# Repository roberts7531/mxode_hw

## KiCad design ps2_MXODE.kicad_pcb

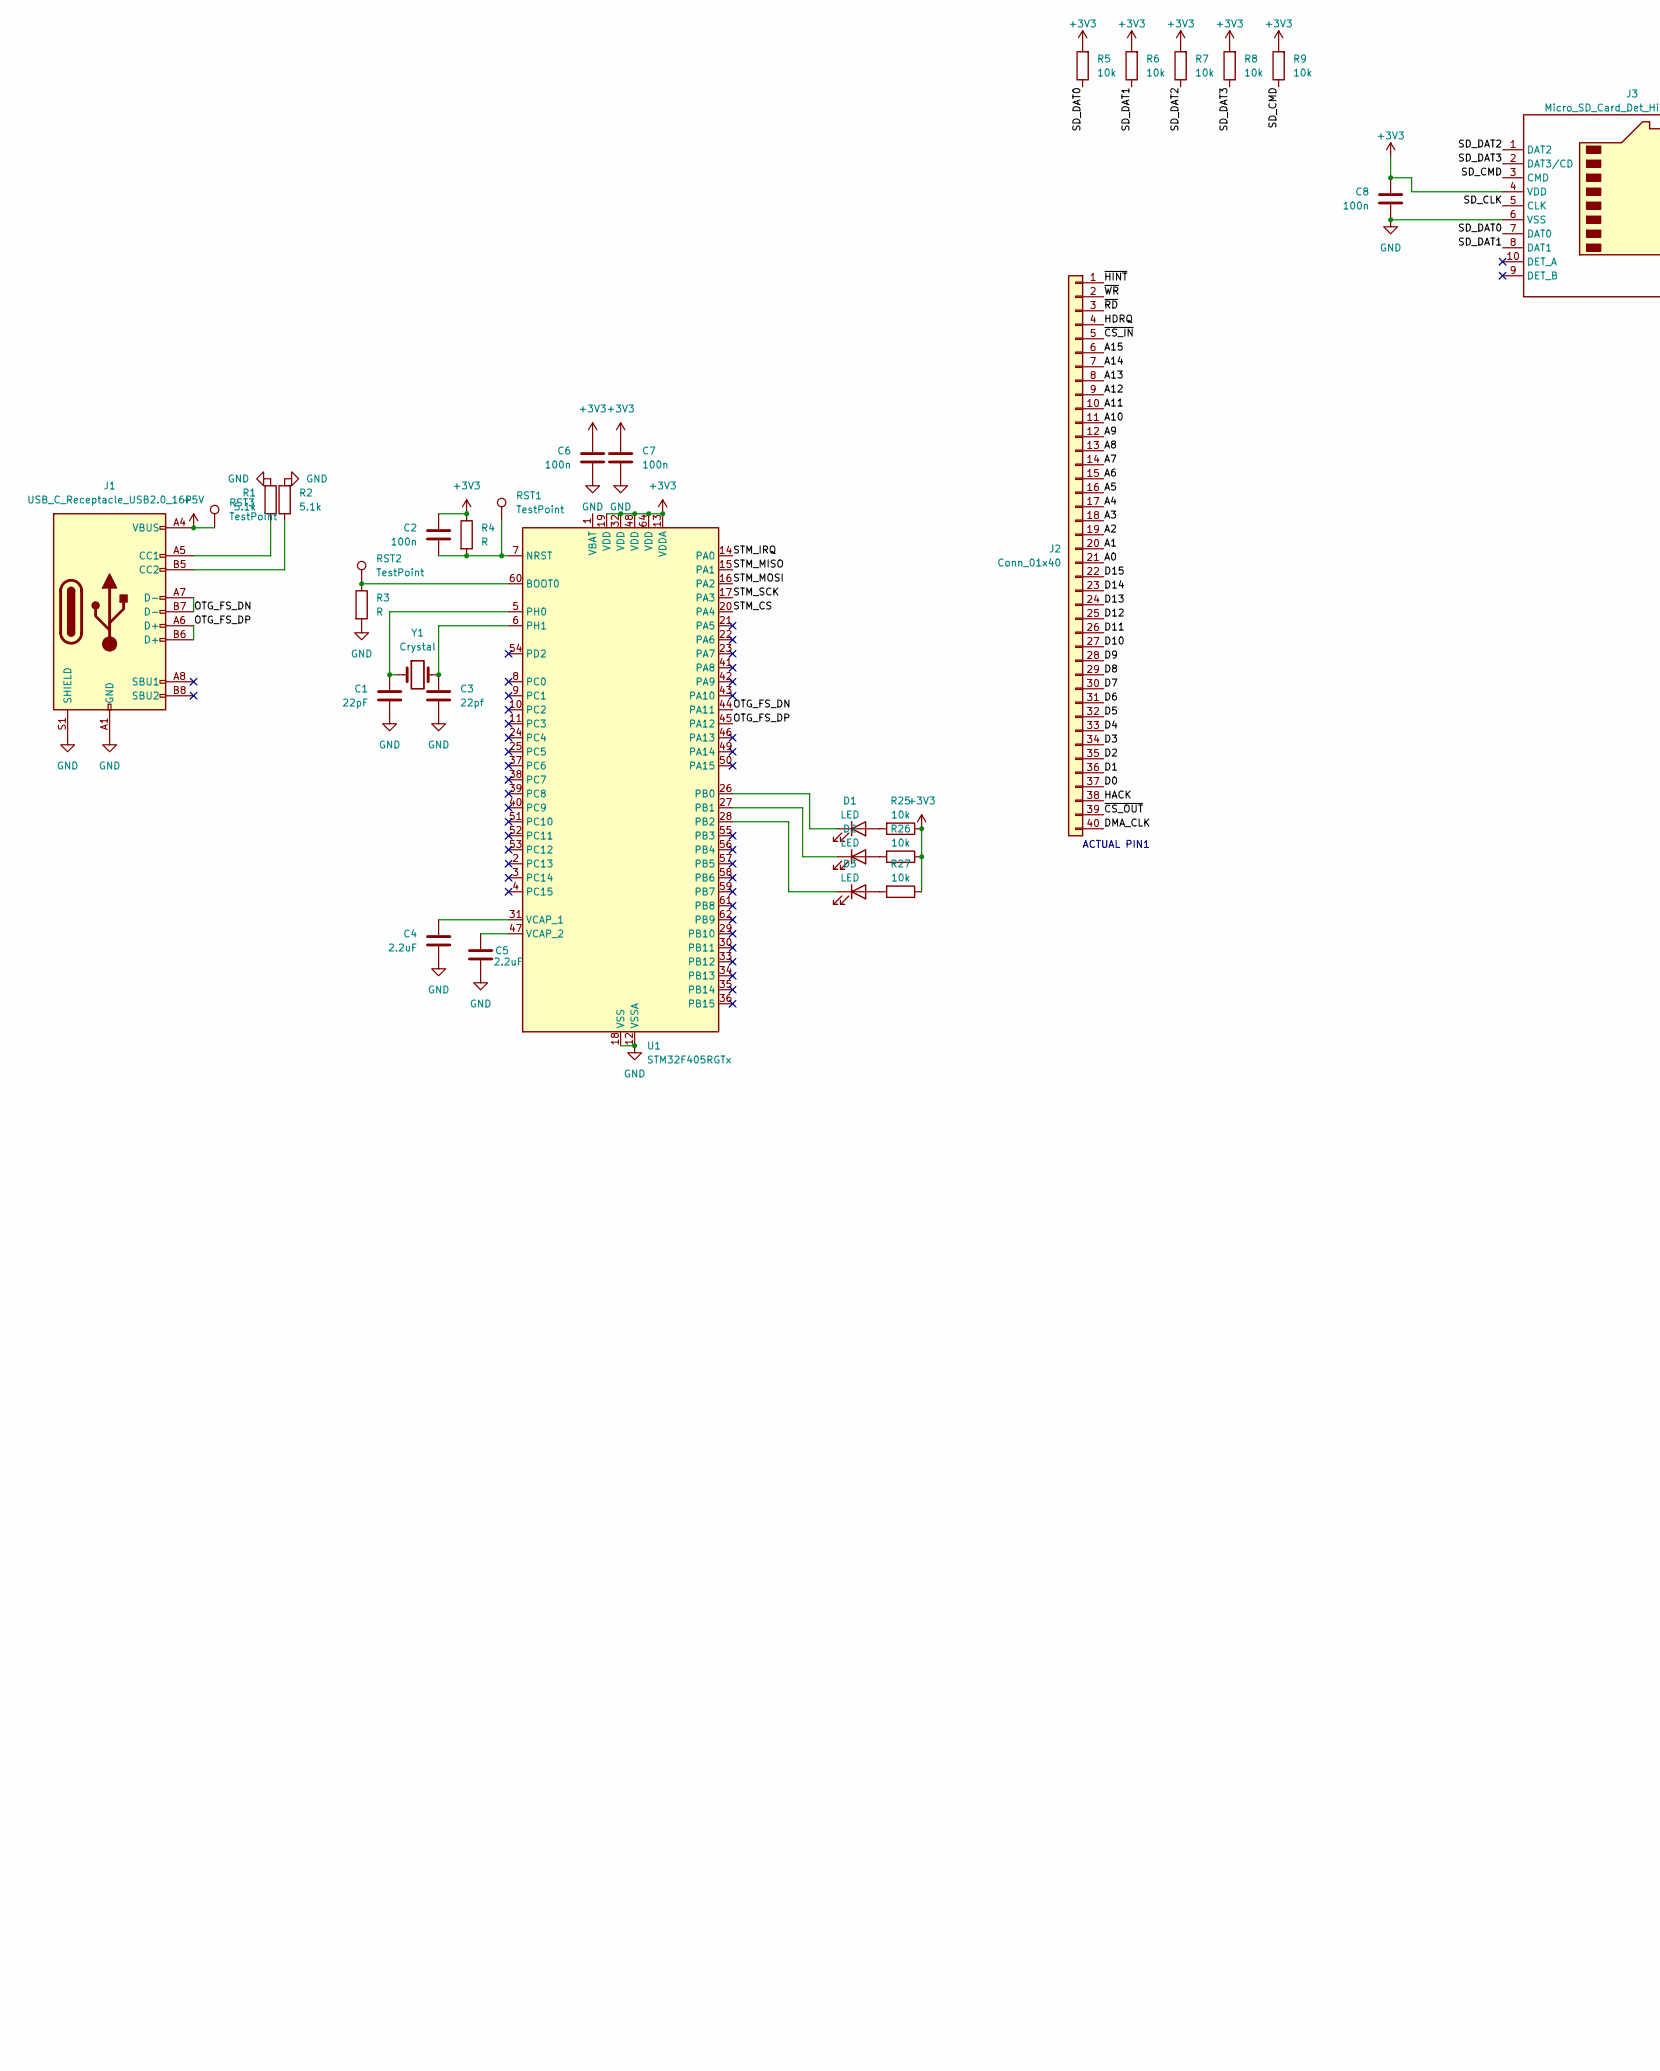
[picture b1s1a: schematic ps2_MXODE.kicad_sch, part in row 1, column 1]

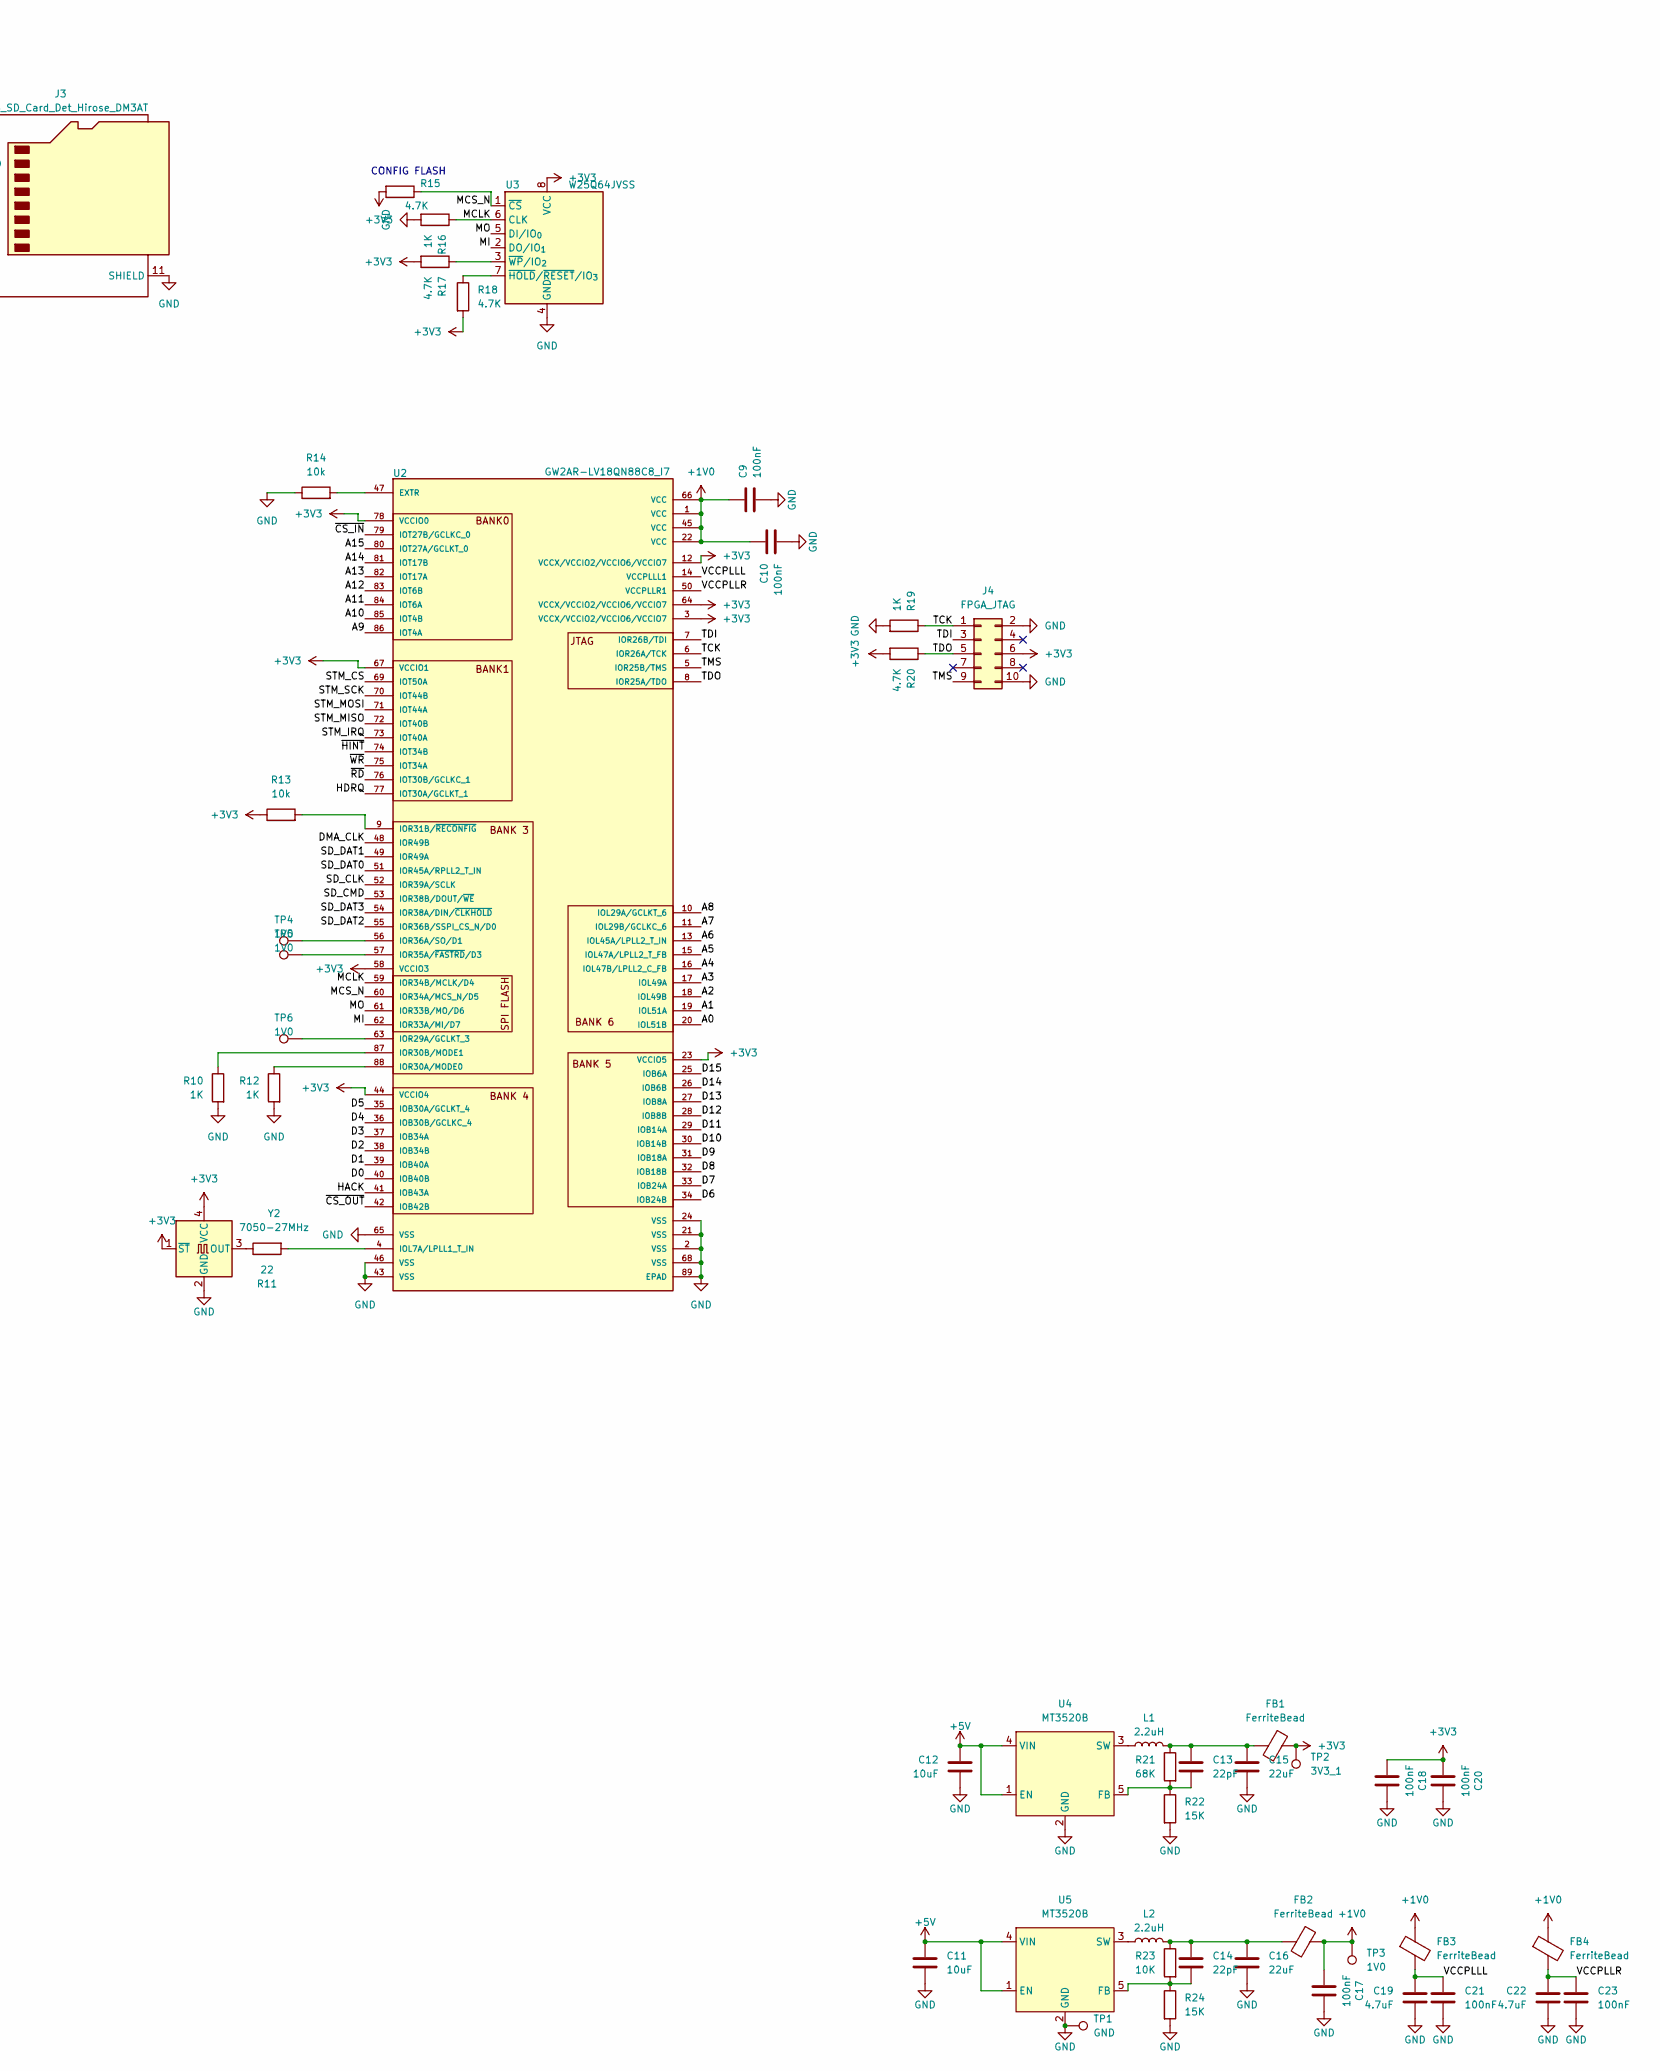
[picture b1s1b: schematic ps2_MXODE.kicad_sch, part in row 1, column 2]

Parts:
C1, C13, C14: 22pF; C_0603_1608Metric_Pad1.08x0.95mm_HandSolder
C2, C6, C7, C8: 100n; C_0603_1608Metric_Pad1.08x0.95mm_HandSolder
C3: 22pf; C_0603_1608Metric_Pad1.08x0.95mm_HandSolder
C4, C5: 2.2uF; C_0603_1608Metric_Pad1.08x0.95mm_HandSolder
C9, C10, C17, C18, C20, C21, C23: 100nF; C_0603_1608Metric_Pad1.08x0.95mm_HandSolder
C11, C12: 10uF; C_0603_1608Metric_Pad1.08x0.95mm_HandSolder
C15, C16: 22uF; C_0603_1608Metric_Pad1.08x0.95mm_HandSolder
C19, C22: 4.7uF; C_0603_1608Metric_Pad1.08x0.95mm_HandSolder
D1, D2, D3: LED; LED_0603_1608Metric_Pad1.05x0.95mm_HandSolder
FB1, FB2, FB3, FB4: FerriteBead; L_0805_2012Metric_Pad1.05x1.20mm_HandSolder
J1: USB_C_Receptacle_USB2.0_16P; USB_C_Receptacle_GCT_USB4105-xx-A_16P_TopMnt_Horizontal
J2: Conn_01x40; Hirose_FH12-40S-0.5SH_1x40-1MP_P0.50mm_Horizontal
J3: Micro_SD_Card_Det_Hirose_DM3AT; microSD_HC_Hirose_DM3D-SF
J4: FPGA_JTAG; PinHeader_2x05_P2.54mm_Vertical
L1, L2: 2.2uH; L_1206_3216Metric_Pad1.22x1.90mm_HandSolder
R1, R2: 5.1k; R_0603_1608Metric_Pad0.98x0.95mm_HandSolder
R3, R4: R; R_0603_1608Metric_Pad0.98x0.95mm_HandSolder
R5, R6, R7, R8, R9, R13, R14, R25, R26, R27: 10k; R_0603_1608Metric_Pad0.98x0.95mm_HandSolder
R10, R12, R16, R19: 1K; R_0603_1608Metric_Pad0.98x0.95mm_HandSolder
R11: 22; R_0603_1608Metric_Pad0.98x0.95mm_HandSolder
R15, R17, R18, R20: 4.7K; R_0603_1608Metric_Pad0.98x0.95mm_HandSolder
R21: 68K; R_0603_1608Metric_Pad0.98x0.95mm_HandSolder
R22, R24: 15K; R_0603_1608Metric_Pad0.98x0.95mm_HandSolder
R23: 10K; R_0603_1608Metric_Pad0.98x0.95mm_HandSolder
RST1, RST2, RST3: TestPoint; PinSocket_1x01_P2.54mm_Vertical
TP1: GND; TestPoint_Pad_1.0x1.0mm
TP2: 3V3_1; TestPoint_Pad_1.0x1.0mm
TP3, TP4, TP5, TP6: 1V0; TestPoint_Pad_1.0x1.0mm
U1: STM32F405RGTx; LQFP-64_10x10mm_P0.5mm
U2: GW2AR-LV18QN88C8_I7; IC_GW2AR-LV18QN88C8_I7; PARTREV 2.4E
U3: W25Q64JVSS; SOIC-8_5.3x5.3mm_P1.27mm
U4, U5: MT3520B; SOT-23-5
Y1: Crystal; Crystal_HC18-U_Vertical
Y2: 7050-27MHz; Oscillator_SMD_SeikoEpson_SG8002CA-4Pin_7.0x5.0mm_HandSolde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

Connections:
+1V0: C9.1, C10.1, C17.2, FB2.1, FB3.1, FB4.1, TP3.1, U2.1 (VCC), U2.22 (VCC), U2.45 (VCC), U2.66 (VCC)
+3V3: C2.2, C6.2, C7.2, C8.2, C18.2, C20.2, FB1.1, J3.4 (VDD), J4.6, R4.1, R5.2, R6.2, R7.2, R8.2, R9.2, R13.1, R15.2, R17.2, R18.2, R20.2, R25.1, R26.1, R27.1, TP2.1, U1.13 (VDDA), U1.19 (VDD), U1.32 (VDD), U1.48 (VDD), U1.64 (VDD), U2.3 (VCCX/VCCIO2/VCCIO6/VCCIO7), U2.12 (VCCX/VCCIO2/VCCIO6/VCCIO7), U2.23 (VCCIO5), U2.44 (VCCIO4), U2.58 (VCCIO3), U2.64 (VCCX/VCCIO2/VCCIO6/VCCIO7), U2.67 (VCCIO1), U2.78 (VCCIO0), U3.8 (VCC), Y2.1 (~ST), Y2.4 (VCC)
+5V: C11.1, C12.1, J1.A4 (VBUS), J1.A9 (VBUS), J1.B4 (VBUS), J1.B9 (VBUS), RST3.1, U4.1 (EN), U4.4 (VIN), U5.1 (EN), U5.4 (VIN)
/A0: J2.21, U2.20 (IOL51B)
/A1: J2.20, U2.19 (IOL51A)
/A2: J2.19, U2.18 (IOL49B)
/A3: J2.18, U2.17 (IOL49A)
/A4: J2.17, U2.16 (IOL47B/LPLL2_C_FB)
/A5: J2.16, U2.15 (IOL47A/LPLL2_T_FB)
/A6: J2.15, U2.13 (IOL45A/LPLL2_T_IN)
/A7: J2.14, U2.11 (IOL29B/GCLKC_6)
/A8: J2.13, U2.10 (IOL29A/GCLKT_6)
/A9: J2.12, U2.86 (IOT4A)
/A10: J2.11, U2.85 (IOT4B)
/A11: J2.10, U2.84 (IOT6A)
/A12: J2.9, U2.83 (IOT6B)
/A13: J2.8, U2.82 (IOT17A)
/A14: J2.7, U2.81 (IOT17B)
/A15: J2.6, U2.80 (IOT27A/GCLKT_0)
/D0: J2.37, U2.40 (IOB40B)
/D1: J2.36, U2.39 (IOB40A)
/D2: J2.35, U2.38 (IOB34B)
/D3: J2.34, U2.37 (IOB34A)
/D4: J2.33, U2.36 (IOB30B/GCLKC_4)
/D5: J2.32, U2.35 (IOB30A/GCLKT_4)
/D6: J2.31, U2.34 (IOB24B)
/D7: J2.30, U2.33 (IOB24A)
/D8: J2.29, U2.32 (IOB18B)
/D9: J2.28, U2.31 (IOB18A)
/D10: J2.27, U2.30 (IOB14B)
/D11: J2.26, U2.29 (IOB14A)
/D12: J2.25, U2.28 (IOB8B)
/D13: J2.24, U2.27 (IOB8A)
/D14: J2.23, U2.26 (IOB6B)
/D15: J2.22, U2.25 (IOB6A)
/DMA_CLK: J2.40, U2.48 (IOR49B)
/HACK: J2.39, U2.42 (IOB42B)
/HDRQ: J2.4, U2.77 (IOT30A/GCLKT_1)
/MCLK: R16.1, U2.59 (IOR34B/MCLK/D4), U3.6 (CLK)
/MCS_N: R15.1, U2.60 (IOR34A/MCS_N/D5), U3.1 (~CS)
/MI: U2.62 (IOR33A/MI/D7), U3.2 (DO/IO_{1})
/MO: U2.61 (IOR33B/MO/D6), U3.5 (DI/IO_{0})
/OTG_FS_DN: J1.A7 (D-), J1.B7 (D-), U1.44 (PA11)
/OTG_FS_DP: J1.A6 (D+), J1.B6 (D+), U1.45 (PA12)
/SD_CLK: J3.5 (CLK), U2.52 (IOR39A/SCLK)
/SD_CMD: J3.3 (CMD), R9.1, U2.53 (IOR38B/DOUT/~WE)
/SD_DAT0: J3.7 (DAT0), R5.1, U2.51 (IOR45A/RPLL2_T_IN)
/SD_DAT1: J3.8 (DAT1), R6.1, U2.49 (IOR49A)
/SD_DAT2: J3.1 (DAT2), R7.1, U2.55 (IOR36B/SSPI_CS_N/D0)
/SD_DAT3: J3.2 (DAT3/CD), R8.1, U2.54 (IOR38A/DIN/~CLKHOLD)
/STM_CS: U1.20 (PA4), U2.69 (IOT50A)
/STM_IRQ: U1.14 (PA0), U2.73 (IOT40A)
/STM_MISO: U1.15 (PA1), U2.72 (IOT40B)
/STM_MOSI: U1.16 (PA2), U2.71 (IOT44A)
/STM_SCK: U1.17 (PA3), U2.70 (IOT44B)
/TCK: J4.1, R19.1, U2.6 (IOR26A/TCK)
/TDI: J4.3, U2.7 (IOR26B/TDI)
/TDO: J4.5, R20.1, U2.8 (IOR25A/TDO)
/TMS: J4.9, U2.5 (IOR25B/TMS)
/VCCPLLL: C19.1, C21.1, FB3.2, U2.14 (VCCPLLL1)
/VCCPLLR: C22.1, C23.1, FB4.2, U2.50 (VCCPLLR1)
/~CS_IN: J2.5, U2.79 (IOT27B/GCLKC_0)
/~CS_OUT: J2.38, U2.41 (IOB43A)
/~HINT: J2.1, U2.74 (IOT34B)
/~RD: J2.3, U2.76 (IOT30B/GCLKC_1)
/~WR: J2.2, U2.75 (IOT34A)
GND: C1.1, C3.1, C4.1, C5.2, C6.1, C7.1, C8.1, C9.2, C10.2, C11.2, C12.2, C15.2, C16.2, C17.1, C18.1, C19.2, C20.1, C21.2, C22.2, C23.2, J1.A1 (GND), J1.A12 (GND), J1.B1 (GND), J1.B12 (GND), J1.S1 (SHIELD), J3.6 (VSS), J3.11 (SHIELD), J4.2, J4.10, R1.2, R2.2, R3.2, R10.2, R12.2, R14.1, R16.2, R19.2, R22.2, R24.2, TP1.1, U1.12 (VSSA), U1.18 (VSS), U1.63 (VSS), U2.2 (VSS), U2.21 (VSS), U2.24 (VSS), U2.43 (VSS), U2.46 (VSS), U2.65 (VSS), U2.68 (VSS), U2.89 (EPAD), U3.4 (GND), U4.2 (GND), U5.2 (GND), Y2.2 (GND)
unnamed: C13.1, C15.1, FB1.2, L1.2, R21.1
unnamed: C14.1, C16.1, FB2.2, L2.2, R23.1
unnamed: D1.2 (A), R25.2
unnamed: D1.1 (K), U1.26 (PB0)
unnamed: D2.2 (A), R26.2
unnamed: D2.1 (K), U1.27 (PB1)
unnamed: D3.2 (A), R27.2
unnamed: D3.1 (K), U1.28 (PB2)
unnamed: J1.A5 (CC1), R1.1
unnamed: J1.B5 (CC2), R2.1
unnamed: R3.1, RST2.1, U1.60 (BOOT0)
unnamed: C2.1, R4.2, RST1.1, U1.7 (NRST)
unnamed: C1.2, U1.5 (PH0), Y1.1
unnamed: C3.2, U1.6 (PH1), Y1.2
unnamed: C4.2, U1.31 (VCAP_1)
unnamed: C5.1, U1.47 (VCAP_2)
unnamed: R14.2, U2.47 (EXTR)
unnamed: R11.2, U2.4 (IOL7A/LPLL1_T_IN)
unnamed: TP6.1, U2.63 (IOR29A/GCLKT_3)
unnamed: R12.1, U2.88 (IOR30A/MODE0)
unnamed: R10.1, U2.87 (IOR30B/MODE1)
unnamed: R13.2, U2.9 (IOR31B/~RECONFIG)
unnamed: TP5.1, U2.57 (IOR35A/~FASTRD/D3)
unnamed: TP4.1, U2.56 (IOR36A/SO/D1)
unnamed: R18.1, U3.7 (~HOLD/~RESET/IO_{3})
unnamed: R17.1, U3.3 (~WP/IO_{2})
unnamed: C13.2, R21.2, R22.1, U4.5 (FB)
unnamed: L1.1, U4.3 (SW)
unnamed: C14.2, R23.2, R24.1, U5.5 (FB)
unnamed: L2.1, U5.3 (SW)
unnamed: R11.1, Y2.3 (OUT)

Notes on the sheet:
CONFIG FLASH
ACTUAL PIN1

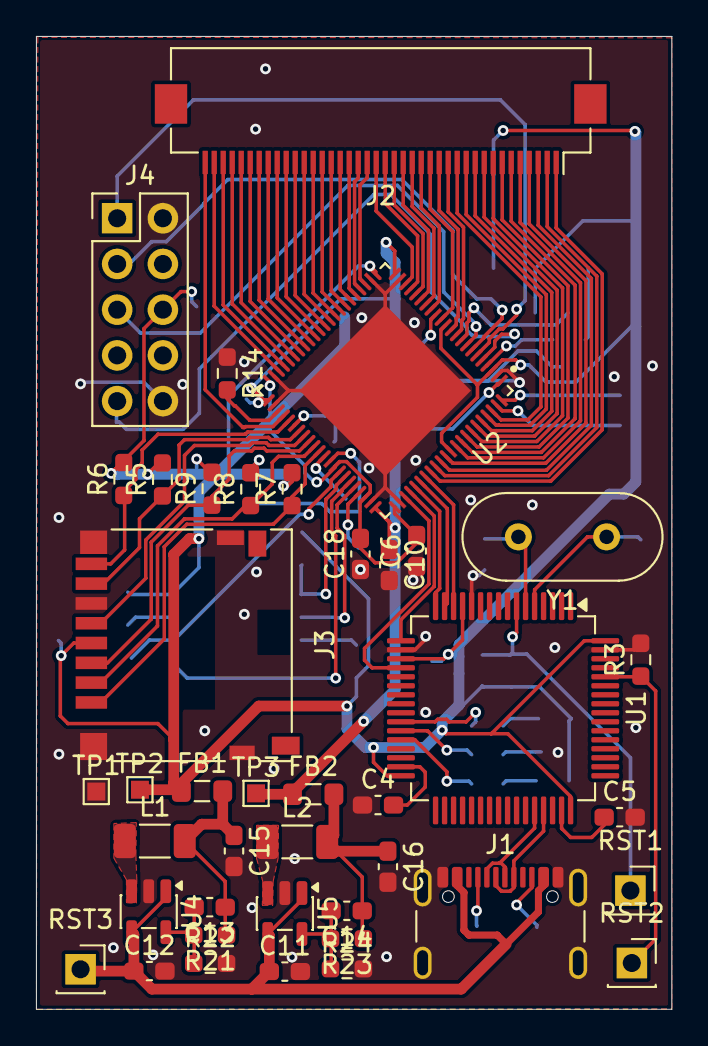
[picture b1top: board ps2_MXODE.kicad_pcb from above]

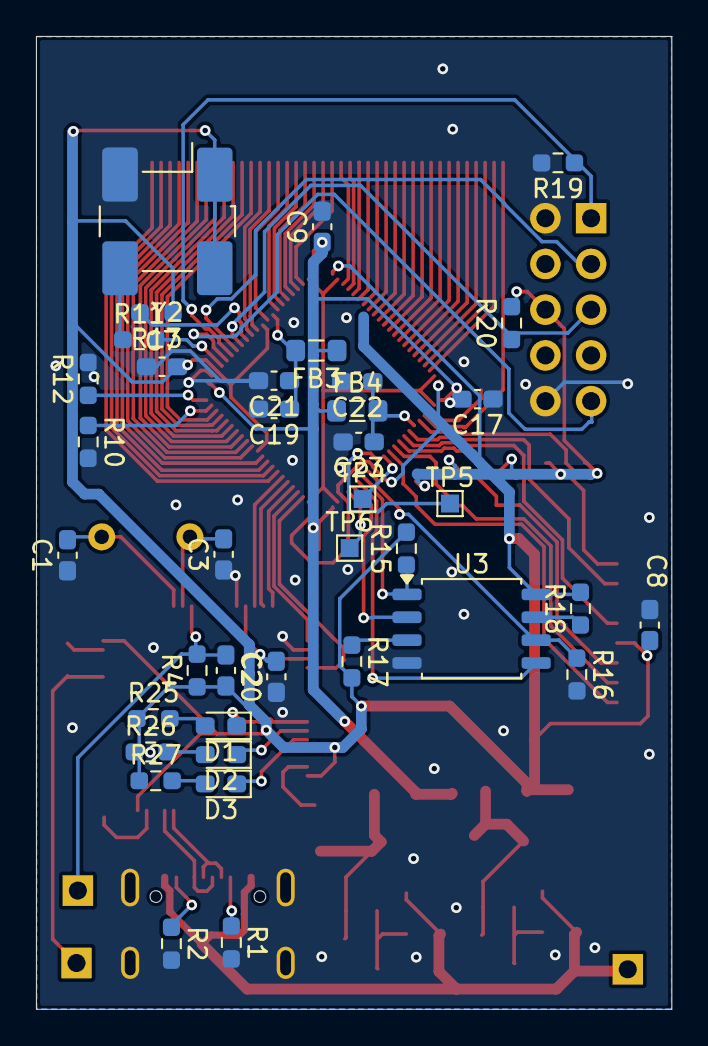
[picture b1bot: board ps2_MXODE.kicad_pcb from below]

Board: 2 copper layers, 35.3 x 54.0 mm, 79 parts (38 on the bottom side), 98 nets.
